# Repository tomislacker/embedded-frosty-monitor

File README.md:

# embedded-frosty-monitor

A portable diagnostic data logger for Frosty Factory 117A/127A/137A frozen-drink
machines. A service tech temporarily installs it inside a machine, lets it run
for days to weeks logging vibration, current draw, temperatures, and
control-state, then pulls the SD card and analyzes the data offline to find
the root cause of an intermittent or hard-to-diagnose fault.

This is not a permanently-installed product. It is a bench/field diagnostic
tool: one unit, moved from machine to machine, that turns "it acts up
sometimes" into a timestamped record of what the compressor, beater motor,
and control chain were actually doing.

## Who this is for

- **Service technicians** who need to capture what a machine does between
  visits, correlate an intermittent symptom (short-cycling, failure to
  freeze, knocking, belt slip) against a timestamp, and bring evidence back
  to the bench instead of a guess.
- **The project owner**, building and maintaining the hardware, firmware, and
  analysis pipeline, and using field data to refine failure-signature
  detection over time.

## What it does

- Logs two AC current channels (beater motor leg, compressor leg) via CT
  clamps, sampled at 1 Hz with transient-burst capture on spikes.
- Logs vibration at the beater drive and the compressor shell via
  accelerometer pods, both as running RMS/peak/band-energy summaries and as
  raw windowed bursts (periodic and trigger-on-event).
- Logs four to five temperatures (cylinder jacket, condenser air in/out,
  ambient, optional hopper) plus compressor discharge line temperature via
  thermocouple.
- Logs drip rate at the drip tube outlet via an optical drop counter — a
  direct, quantitative read on rear cylinder seal wear — plus optional
  under-machine moisture and refrigerant-gas-sensor add-ons.
- Logs digital AC-presence state on the beater leg and the 24VAC contactor
  coil, so control-chain behavior (is the compressor actually trying to run)
  is visible alongside the analog channels.
- Timestamps everything against a battery-backed RTC, independent of network
  time.
- Writes a self-describing record set to a microSD card: a manifest, daily
  CSV channel logs, binary vibration bursts, a vibration summary CSV, and a
  JSONL event log — no proprietary format, no required companion service.
- Lets the tech mark a moment as notable with a physical event button,
  producing a first-class timestamped incident marker independent of any
  later annotation.
- Splits into a reusable "logger core" (the electronics, in an IP65
  enclosure) and cheap, detachable "sensor pods" that take the grease/sugar
  contamination and get replaced, not the core.

## Product tiers

DAQ Pro, described above, is one of four hardware tiers built on the same
firmware, data format, and analysis stack — see
[docs/product-line.md](docs/product-line.md) for the full comparison and
[ADR 0007](docs/adr/0007-product-tier-strategy.md) for the decision behind
the tier structure.

| Tier | BOM (est.) | Install | Status |
|---|---|---|---|
| 1 — Guard | ≈$26 | Permanent, every machine | Designed |
| 2 — Logger | ≈$55–70 | Permanent | Designed |
| 3 — DAQ Pro | $152.60 | Portable (this repo's flagship) | **Built** |
| 4 — Live | $160 WiFi / ≈$210 cellular | Permanent + connectivity | Firmware in progress |

## Repo map

| Path | Owner content | Description |
|---|---|---|
| [`docs/`](docs/) | this doc set | Architecture, ADRs, safety, roadmap, install guides |
| [`docs/architecture/`](docs/architecture/overview.md) | this doc set | System overview and data-flow diagrams |
| [`docs/adr/`](docs/adr/template.md) | this doc set | Architecture decision records |
| [`docs/hardware/`](docs/hardware/) | hardware docs | Wiring, enclosure, sensor placement, BOM |
| [`docs/firmware/`](docs/firmware/architecture.md) | firmware docs | Firmware architecture and on-card data format spec |
| [`docs/install-guides/`](docs/install-guides/137A.md) | install-guide docs | Per-model install procedures (117A/127A/137A) |
| `firmware/` | firmware team | PlatformIO project: FreeRTOS tasks, drivers, storage sinks |
| `hardware/` | hardware team | Schematics, enclosure files, BOM source |
| [`pcb/guard/`](pcb/guard/README.md) | PCB (experimental) | Guard tier custom PCB: SKiDL schematic, scripted layout/DRC, agent-driven design experiment -- unreviewed draft, not fab-ready |
| `analysis/` | analysis team | Offline Python analysis pipeline and tests |

## Quickstart

### Firmware

```
cd firmware
pio run -e esp32-s3-devkitc-1
```

See [`docs/firmware/architecture.md`](docs/firmware/architecture.md) for the
task layout and [`docs/firmware/data-format-spec.md`](docs/firmware/data-format-spec.md)
for the on-card record format.

### Analysis

```
python -m venv .venv && . .venv/bin/activate
pip install -e analysis/
pytest analysis/tests
```

### Installing on a machine

Read [`docs/safety.md`](docs/safety.md) before touching a machine. Then
follow the model-specific procedure in
[`docs/install-guides/137A.md`](docs/install-guides/137A.md).

## Project status

**M0 — docs and repo skeleton.** No hardware has been built or bench-tested
yet; this stage is establishing the architecture, decisions, and safety
constraints the rest of the project builds on.

Milestones:

- **M0** — Docs and skeleton. Architecture, ADRs, safety doc, roadmap; repo
  layout in place. *(current)*
- **M1** — Bench bring-up of real drivers: each sensor/breakout talking to
  the ESP32-S3 on a breadboard, no enclosure, no machine.
- **M2** — Enclosure integration: logger core assembled in its IP65 box,
  sensor pods wired and connectorized, full firmware pipeline exercised on
  the bench.
- **M3** — Bench test on a spare 137A: full install procedure rehearsed on a
  non-production machine.
- **M4** — First field deployment: unit installed in a live machine at a
  customer site for a real diagnostic case.
- **M5** — 117A/127A validation: confirm the sensor placements and
  thresholds generalize across the other two chassis sizes.

See [`docs/roadmap.md`](docs/roadmap.md) for what comes after M5.

## License

Licensed under the Apache License, Version 2.0 — see [`LICENSE`](LICENSE).
Copyright 2026 Ben Tomasik (tomislacker).

You may use, reproduce, modify, and distribute this work, including
commercially, provided you retain the copyright notice, the license text, and
the [`NOTICE`](NOTICE) file in any redistribution, and state any changes you
made. The license covers everything in this repo: firmware, the analysis
package, hardware BOM and pinmap, and the doc set.

The license's "AS IS" disclaimer applies to the hardware designs and install
procedures as much as to the code. This device is installed inside machines
carrying line-voltage AC and refrigerant under pressure — read
[`docs/safety.md`](docs/safety.md) and take responsibility for your own build.

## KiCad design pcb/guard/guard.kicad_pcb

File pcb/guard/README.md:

# FrostSight Guard rev A (draft) -- PCB (experimental)

> **This is an unreviewed draft. It has not been checked by a human EE and
> must not be fabricated as-is.** See
> [docs/compliance.md](../../docs/compliance.md) for the certification
> context this board eventually has to clear, and get a professional EE
> review before sending anything here to a fab. This whole `pcb/guard/`
> tree is an experiment in agent-driven PCB design with a scripted
> verification loop (SKiDL schematic -> pcbnew layout -> `kicad-cli` DRC
> + renders) -- it is deliberately optimized for *reviewability*, not for
> being fab-ready out of the box.

This is the first custom PCB for the Guard tier described in
[docs/product-line.md](../../docs/product-line.md) (Tier 1): a permanent,
every-machine monitor board built around a pre-certified ESP32-C3-MINI-1
module. SELV only -- nothing above 5V ever touches this board.

## Honest status

**What's done:**

- A complete SKiDL schematic ([`schematic.py`](schematic.py)) covering
  every circuit block in the spec: MCU, USB-C power+data with ESD
  protection, 3.3V regulation, CT current-sense front end, 2x DS18B20
  headers, drip-counter header, status/alert LEDs, ack/BOOT/RESET
  buttons, I2C (Qwiic) and UART expansion headers, 2x M3 mounting holes.
- SKiDL ERC passes clean: **0 errors, 0 warnings** (two expected
  advisory warnings are pre-empted with documented, reviewed waivers --
  see the ERC section at the bottom of `schematic.py`).
- A generated KiCad netlist (`guard.net`) and a from-scratch `.kicad_pcb`
  ([`build_board.py`](build_board.py)) with a deliberate, documented
  placement for all 43 components, a ground pour on both copper layers,
  an antenna keep-out rule area, and a scripted attempt at routing the
  short, unambiguous connections.
- `kicad-cli pcb drc` on the routed board: **0 electrical violations**
  (no shorting, no copper clearance violations, no crossing tracks, no
  out-of-range drills/holes). 3 non-electrical DRC nags remain --
  1 courtyard overlap (a mounting hole's 3.45mm-radius assembly-exclusion
  circle just can't clear everything on a board this dense) and 2
  silkscreen-clipped-by-edge nags on the CT jack's own library
  silkscreen, which is expected for a connector whose body intentionally
  overhangs the board edge. Full detail: `drc_report.json`, or run
  `check.sh` yourself.
- Renders inspected and iterated on twice: the first pass had the USB-C
  connector's mating face sitting ~2mm inboard of the board edge instead
  of flush with it; the second pass (current state) fixed that. See
  `renders/top.png` / `renders/bottom.png` / `.svg`.
- A [`bom.csv`](bom.csv) with per-line LCSC estimates and a rollup
  compared against the tier's cost targets.

**What's not done / known limitations:**

- **Routing is partial, on purpose.** The scripted router in
  `build_board.py` only commits a track when it's confident the hop is
  short and won't clip a foreign pad, cross another net's track, or run
  through the antenna keep-out -- otherwise it leaves the connection as
  ratsnest rather than fake a route. Current numbers (regenerate with
  `check.sh` to reconfirm): **20 of 65 point-to-point hops routed**, 3 of
  25 signal/power nets fully routed, 6 partially, 16 left entirely as
  ratsnest (46 unconnected items in the DRC report). GND is handled
  entirely by copper pour instead of discrete traces, which is normal
  practice, not a routing gap. **Finishing routing by hand in the KiCad
  GUI is the single biggest next step before this is fab-ready.**
- **Board is 70x55mm, not the spec's <=60x45mm target.** This is a
  direct, documented consequence of a library gap, not a claim that the
  real board can't hit spec -- see the MCU footprint note below.
- **No thermal analysis.** Nothing has been checked for the AMS1117's
  dropout/dissipation under sustained WiFi TX bursts, copper pour
  thermal relief, or enclosure thermal behavior.
- **No real DFM/panelization review**, no impedance analysis on the USB
  differential pair, no BOM stock/lead-time check beyond LCSC part-number
  estimates.
- **1 cosmetic courtyard overlap and 2 cosmetic silkscreen nags** remain
  in DRC, as noted above -- neither is electrical.

## The MCU footprint substitution -- read this before opening the board

The spec calls for an **ESP32-C3-MINI-1** module. KiCad 10's stock
libraries do not ship a MINI-1 symbol or footprint (they have
ESP32-C3-WROOM-02, ESP32-C3-DevKitM-1, and ESP32-C6-MINI-1, but not
C3-MINI-1). This design uses **RF_Module:ESP32-C3-WROOM-02** as a
stand-in everywhere U1 appears:

- Same ESP32-C3 SoC, same GPIO numbering and strapping behavior
  (GPIO0-10, 18/19 USB, 20/21 UART0) -- every net connection and the GPIO
  table below are electrically representative of the real MINI-1.
- The WROOM-02 footprint is physically **larger** (~18.2x20.2mm) than the
  real MINI-1 (~15.4x20.5mm) and its castellated pad positions do not
  match MINI-1's datasheet pad map. That size difference is the reason
  this board is 70x55mm instead of the spec's 60x45mm target, and the
  antenna keep-out zone in `build_board.py` is sized against the
  WROOM-02's geometry, not MINI-1's.

**Before fabrication, EE review must swap in a real ESP32-C3-MINI-1
footprint** (built from Espressif's datasheet pad map) and re-verify the
antenna keep-out against MINI-1's actual RF section location. Doing that
should let the board shrink back toward the 60x45mm target.

## GPIO assignment (authoritative)

| GPIO | Net | Function | Notes |
|---|---|---|---|
| GPIO0 | `CT_SIG` | ADC1_CH0, CT current sense | through anti-alias RC + bias network |
| GPIO1 | `ONEWIRE` | DS18B20 bus (both JST-XH chains, shared) | single 4.7k pull-up |
| GPIO2 | -- | **reserved, unpopulated** | strapping pin; no load at boot |
| GPIO3 | `DRIP_SIG` | drip-counter pulse in | RC debounced |
| GPIO4 | `LED_STATUS_A` | status LED (green) | ADC1_CH4 unused as analog |
| GPIO5 | `LED_ALERT_A` | alert LED (red) | |
| GPIO6 | `I2C_SCL` | Qwiic expansion | |
| GPIO7 | `I2C_SDA` | Qwiic expansion | |
| GPIO8 | -- | **reserved, unpopulated** | strapping pin; no load at boot |
| GPIO9 | `BTN_BOOT` | BOOT button | conventional strap-to-GND use |
| GPIO10 | `BTN_ACK` | user acknowledge button | |
| GPIO18 | `USB_DM` | native USB D- | fixed function |
| GPIO19 | `USB_DP` | native USB D+ | fixed function |
| GPIO20 | `UART_RX` | debug header | |
| GPIO21 | `UART_TX` | debug header | |
| EN | `EN_RESET` | RESET button (EN-to-GND) | 10k pull-up + 100nF per Espressif ref design |

GPIO2 and GPIO8 -- the two strapping pins other than BOOT/GPIO9 -- are
left completely unpopulated: no resistor, no connector, nothing that
could present a load at boot, per the board spec.

## Design-for-compliance notes

- **SELV only.** Everything on this board runs at 5V or below; mains
  never touches it. USB-C is configured 5V-only via 5.1k CC pulldowns,
  no PD negotiation.
- **Pre-certified module, no custom antenna.** The MCU's onboard PCB
  antenna is used as-is; this design does not attempt a custom antenna,
  which is what keeps the module's existing FCC modular approval valid.
- **ESD protection on every user-touchable connector path**: USBLC6-2
  class protection on USB VBUS/D+/D-; a BAT54S dual-Schottky clamp on the
  CT sense line.
- **No exposed copper test points near the board edge mounting area.**
  Both M3 mounting holes use the `MountingHole_3.2mm_M3` footprint, which
  is a bare drilled hole with no copper pad.

## Repo map

| File | What it is |
|---|---|
| `schematic.py` | SKiDL design-as-code schematic. Run it to regenerate `guard.net`. Heavily commented -- read this first, it's the reviewable schematic. |
| `guard.net` | Generated KiCad netlist (do not hand-edit; regenerate from `schematic.py`). |
| `build_board.py` | pcbnew layout script: placement, ground pours, antenna keep-out, scripted routing. Fully re-runnable -- regenerates `guard.kicad_pcb` from scratch every time. |
| `guard.kicad_pcb` / `.kicad_pro` / `.kicad_prl` | Generated PCB + project files. Open `guard.kicad_pcb` (or the `.kicad_pro`) in KiCad's PCB Editor to inspect/hand-route. |
| `check.sh` | The verification gate: schematic ERC -> board build -> DRC -> renders, in order, with a real non-zero exit on an electrical problem. |
| `drc_report.json` | Latest `kicad-cli pcb drc` output (regenerated by `check.sh`). |
| `bom.csv` | Bill of materials with LCSC estimates and a cost rollup. |
| `renders/` | `top.png` / `bottom.png` (3D-style renders) and `top.svg` / `bottom.svg` (flat copper+silk+edge views), regenerated by `check.sh`. |

## How to run `check.sh`

You need:

1. **KiCad 10** with `kicad-cli` on `PATH`, and its bundled `pcbnew`
   Python module importable from a system `python3` (verify with
   `python3 -c "import pcbnew"`).
2. A separate Python environment with **SKiDL** installed, pointed at
   KiCad's symbol libraries:

   ```
   python3 -m venv pcb/guard/venv   # or wherever you keep it
   source pcb/guard/venv/bin/activate
   pip install skidl
   ```

   SKiDL and `pcbnew` have never needed to coexist in one interpreter
   for this project -- `schematic.py` runs under the SKiDL venv,
   `build_board.py` runs under the system `python3` that has `pcbnew`.
   `schematic.py` itself hard-codes `KICAD_SYMBOL_DIR` (defaulting to
   `/usr/share/kicad/symbols`) so it doesn't depend on shell env vars.

3. Then, from `pcb/guard/`:

   ```
   ./check.sh
   ```

   `check.sh` looks for a SKiDL-capable interpreter at `./venv/bin/python3`
   first, then falls back to whatever's on `PATH`; override with
   `SKIDL_PYTHON=/path/to/python3`. It looks for `pcbnew` on plain
   `python3` by default; override with `PCBNEW_PYTHON=/path/to/python3`
   if yours lives somewhere else.

## How to open this in the KiCad GUI

- **PCB only:** open `guard.kicad_pcb` (or `guard.kicad_pro`) directly in
  KiCad's PCB Editor. Placement, pours, the antenna keep-out zone, and
  whatever the scripted router routed are all there to inspect, and it's
  a normal KiCad board file -- hand-routing the rest, nudging placement,
  and rerunning DRC all work exactly like any other KiCad project.
- **No `.kicad_sch` exists.** The schematic is `schematic.py` itself (the
  SKiDL source) plus the generated `guard.net` netlist -- there's no
  KiCad schematic file to open in the Schematic Editor. If a real KiCad
  schematic sheet becomes useful later (e.g. so a human can redline it
  directly), generating one from `guard.net` is a reasonable next step,
  not something this experiment did.

## Next steps

1. **Professional EE review** (this board's one paid hour) -- start with
   this README's limitations list and the MCU footprint-substitution
   note above.
2. **Swap in a real ESP32-C3-MINI-1 footprint** built from Espressif's
   datasheet pad map, re-verify the antenna keep-out against it, and see
   how close the board comes back to the 60x45mm target.
3. **Finish routing.** 20 of 65 hops are routed; the rest need either a
   smarter scripted router or hand-routing in the KiCad GUI.
4. **JLCPCB DFM upload** once routing is complete and the footprint swap
   above is done -- their DFM checker will catch fab-specific issues
   (soldermask, silkscreen-on-pad, panelization) that a generic DRC run
   doesn't.

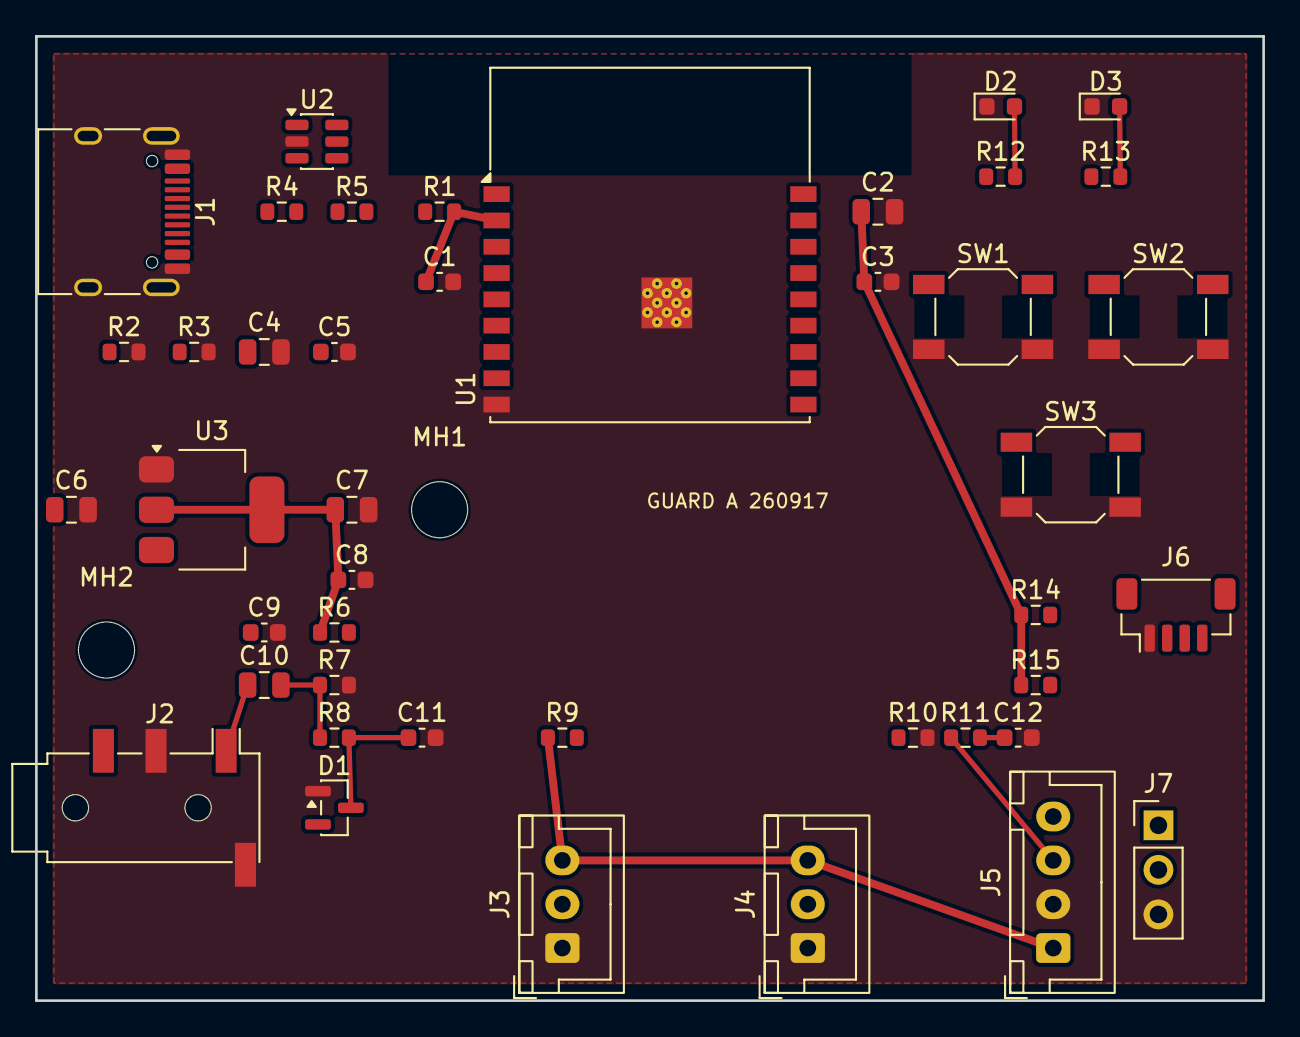
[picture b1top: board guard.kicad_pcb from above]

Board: 2 copper layers, 70.0 x 55.0 mm, 45 parts (0 on the bottom side), 26 nets.

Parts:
C1, C3, C5, C8, C11, C12: 100nF; C_0603_1608Metric
C2, C4, C6, C10: 10uF; C_0805_2012Metric
C7: 22uF; C_0805_2012Metric
C9: 1uF; C_0603_1608Metric
D1: BAT54S; SOT-23
D2: Status LED (green); LED_0603_1608Metric
D3: Alert LED (red); LED_0603_1608Metric
J1: USB-C receptacle (5V power + USB2.0 data, no PD); USB_C_Receptacle_HRO_TYPE-C-31-M-12
J2: 3.5mm TRS (SCT-013-020 burden output, 1V RMS @ ra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; Jack_3.5mm_PJ320D_Horizontal
J3: DS18B20 chain 1 (pin1 GND / pin2 DQ / pin3 3V3); JST_XH_B3B-XH-A_1x03_P2.50mm_Vertical
J4: DS18B20 chain 2 (pin1 GND / pin2 DQ / pin3 3V3); JST_XH_B3B-XH-A_1x03_P2.50mm_Vertical
J5: Drip counter (pin1 3V3 / pin2 GND / pin3 SIG / pi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; JST_XH_B4B-XH-A_1x04_P2.50mm_Vertical
J6: I2C expansion, Qwiic pinout (pin1 GND / pin2 3V3 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; JST_SH_BM04B-SRSS-TB_1x04-1MP_P1.00mm_Vertical
J7: UART debug (pin1 TX / pin2 RX / pin3 GND); PinHeader_1x03_P2.54mm_Vertical
MH1, MH2: MountingHole_3.2mm_M3
R1, R6, R7, R10: 10k; R_0603_1608Metric
R2, R3: 5.1k; R_0603_1608Metric
R4, R5: 22; R_0603_1608Metric
R8, R11: 1k; R_0603_1608Metric
R9, R14, R15: 4.7k; R_0603_1608Metric
R12, R13: 330; R_0603_1608Metric
SW1: Ack button (user); SW_SPST_SKQG_WithoutStem
SW2: BOOT button (GPIO9, conventional strap-to-GND); SW_SPST_SKQG_WithoutStem
SW3: RESET button (EN-to-GND); SW_SPST_SKQG_WithoutStem
U1: ESP32-C3-MINI-1 (schematic symbol: ESP32-C3-WROOM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; ESP32-C3-WROOM-02
U2: USBLC6-2SC6; SOT-23-6
U3: AMS1117-3.3; SOT-223

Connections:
+3V3: C2.1, C3.1, C7.1, C8.1, D1.2, J3.3, J4.3, J5.1, J6.2, R1.1, R6.1, R9.1, R14.1, R15.1, U1.1, U3.2, U3.4
BTN_ACK: SW1.1, U1.10
BTN_BOOT: SW2.1, U1.8
CC1: J1.A5, R2.1
CC2: J1.B5, R3.1
CT_BIAS: C9.1, C10.2, R6.2, R7.1, R8.1
CT_RAW: C10.1, J2.T
CT_SIG: C11.1, D1.3, R8.2, U1.18
DRIP_RAW: J5.3, R10.1, R11.1
DRIP_SIG: C12.1, R11.2, U1.15
EN_RESET: C1.1, R1.2, SW3.1, U1.2
GND: C1.2, C2.2, C3.2, C4.2, C5.2, C6.2, C7.2, C8.2, C9.2, C11.2, C12.2, D1.1, D2.1, D3.1, J1.A1, J1.A12, J1.B1, J1.B12, J1.SH, J2.R1, J2.S, J3.1, J4.1, J5.2, J6.1, J7.3, R2.2, R3.2, R7.2, R10.2, SW1.2, SW2.2, SW3.2, U1.9, U1.19, U2.2, U3.1
I2C_SCL: J6.4, R14.2, U1.5
I2C_SDA: J6.3, R15.2, U1.6
LED_ALERT_A: R13.1, U1.4
LED_STATUS_A: R12.1, U1.3
unnamed: D2.2, R12.2
unnamed: D3.2, R13.2
ONEWIRE: J3.2, J4.2, R9.2, U1.17
UART_RX: J7.2, U1.11
UART_TX: J7.1, U1.12
USB_DM: R5.2, U1.13
USB_DM_CONN: J1.A7, J1.B7, R5.1, U2.3, U2.4
USB_DP: R4.2, U1.14
USB_DP_CONN: J1.A6, J1.B6, R4.1, U2.1, U2.6
VBUS: C4.1, C5.1, C6.1, J1.A4, J1.A9, J1.B4, J1.B9, U2.5, U3.3

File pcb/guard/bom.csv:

Designators,Qty,Value,Footprint,LCSC Part # (estimate unless noted),Unit Price USD (est.),Ext. Price USD (est.),Notes
U1,1,ESP32-C3-MINI-1,RF_Module:ESP32-C3-MINI-1 (schematic uses ESP32-C3-WROOM-02 stand-in -- see README),C2934569,1.85,1.85,"Pre-certified module, onboard PCB antenna. Real MINI-1 footprint not in stock KiCad libs -- see README limitations."
J1,1,USB-C receptacle 16P,Connector_USB:USB_C_Receptacle_HRO_TYPE-C-31-M-12,C165948,0.12,0.12,5V/USB2.0 only; no PD IC
U2,1,USBLC6-2SC6,Package_TO_SOT_SMD:SOT-23-6,C2827654,0.06,0.06,USB ESD protection (VBUS/D+/D-)
U3,1,AMS1117-3.3,Package_TO_SOT_SMD:SOT-223,C6186,0.06,0.06,>=1A rated 3.3V LDO
D1,1,BAT54S,Package_TO_SOT_SMD:SOT-23,C8598,0.02,0.02,Dual Schottky clamp on CT_SIG
D2,1,LED green 0603,LED_SMD:LED_0603_1608Metric,C72043,0.01,0.01,Status LED
D3,1,LED red 0603,LED_SMD:LED_0603_1608Metric,C2286,0.01,0.01,Alert LED
"SW1,SW2,SW3",3,Tactile switch SMD 6x6mm,Button_Switch_SMD:SW_SPST_SKQG_WithoutStem,C318884,0.03,0.09,Ack / BOOT / RESET buttons
J2,1,3.5mm TRS jack (THT),Connector_Audio:Jack_3.5mm_PJ320D_Horizontal,C144396,0.10,0.10,SCT-013-020 CT input; likely hand-solder/THT reflow, not a basic SMT part
"J3,J4",2,JST-XH 3-pin vertical (THT),Connector_JST:JST_XH_B3B-XH-A_1x03_P2.50mm_Vertical,C158126,0.05,0.10,DS18B20 chain headers
J5,1,JST-XH 4-pin vertical (THT),Connector_JST:JST_XH_B4B-XH-A_1x04_P2.50mm_Vertical,C158128,0.06,0.06,Drip counter header
J6,1,JST-SH 4-pin vertical (THT),Connector_JST:JST_SH_BM04B-SRSS-TB_1x04-1MP_P1.00mm_Vertical,C160404,0.06,0.06,I2C/Qwiic expansion header
J7,1,Pin header 1x3 2.54mm (THT),Connector_PinHeader_2.54mm:PinHeader_1x03_P2.54mm_Vertical,C124378,0.02,0.02,UART debug header
"R4,R5",2,22R 0603,Resistor_SMD:R_0603_1608Metric,C25744,0.002,0.004,USB D+/D- series termination
"R12,R13",2,330R 0603,Resistor_SMD:R_0603_1608Metric,C22775,0.002,0.004,LED series resistors
"R8,R11",2,1k 0603,Resistor_SMD:R_0603_1608Metric,C21190,0.002,0.004,CT anti-alias / drip series
"R9,R14,R15",3,4.7k 0603,Resistor_SMD:R_0603_1608Metric,C23162,0.002,0.006,1-Wire pull-up / I2C pull-ups
"R2,R3",2,5.1k 0603,Resistor_SMD:R_0603_1608Metric,C25900,0.002,0.004,USB-C CC1/CC2 pulldowns
"R1,R6,R7,R10",4,10k 0603,Resistor_SMD:R_0603_1608Metric,C25741,0.002,0.008,EN pull-up / CT bias divider / drip pulldown
"C1,C3,C8,C11,C12",5,100nF 0603,Capacitor_SMD:C_0603_1608Metric,C14663,0.003,0.015,Decoupling / anti-alias / debounce
C9,1,1uF 0603,Capacitor_SMD:C_0603_1608Metric,C15849,0.01,0.01,CT bias node decoupling
"C2,C4,C6,C10",4,10uF 0805,Capacitor_SMD:C_0805_2012Metric,C19702,0.02,0.08,Bulk decoupling / AC-coupling
C7,1,22uF 0805,Capacitor_SMD:C_0805_2012Metric,C45783,0.03,0.03,AMS1117 output cap
"MH1,MH2",2,M3 mounting hole (NPTH),MountingHole:MountingHole_3.2mm_M3,N/A -- drilled feature not a stocked part,0.00,0.00,No copper at hole per compliance note
,,,,,,,
,,,,,COMPONENTS SUBTOTAL,2.73,
,,,,,Bare PCB fab (2-layer 70x55mm; small-batch estimate),2.00,
,,,,,JLCPCB SMT assembly service fee (amortized; small-batch estimate),9.00,
,,,,,ESTIMATED PCBA TOTAL (small batch),13.73,
,,,,,,,
,,,,,vs. docs/product-line.md Guard module-based BOM (~$26; includes enclosure/PSU/wiring not this PCB),,
,,,,,vs. docs/product-line.md $10-15 PCBA target,within target band at small-batch assembly pricing assumed above,,

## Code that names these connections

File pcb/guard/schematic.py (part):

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
GPIO ASSIGNMENT (authoritative -- mirrored in README.md)

  GPIO0   ADC1_CH0  CT_SIG        analog, through anti-alias RC + bias net
  GPIO1             ONEWIRE       DS18B20 bus (both JST-XH chains, shared)
  GPIO2             RESERVED      strapping pin -- left unconnected (NC)
  GPIO3             DRIP_SIG      drip-counter pulse in, RC debounced
  GPIO4   ADC1_CH4  LED_STATUS    green status LED (ADC channel unused)
  GPIO5             LED_ALERT     red alert LED
  GPIO6             I2C_SCL       Qwiic expansion header
  GPIO7             I2C_SDA       Qwiic expansion header
  GPIO8             RESERVED      strapping pin -- left unconnected (NC)
  GPIO9             BTN_BOOT      BOOT button, conventional strap-to-GND use
  GPIO10            BTN_ACK       user acknowledge button
  GPIO18            USB_DM        native USB, fixed function
  GPIO19            USB_DP        native USB, fixed function
  GPIO20            UART_RX       debug header
  GPIO21            UART_TX       debug header
  EN                RESET         reset button (EN-to-GND) + 10k pull-up +
                                   100nF per Espressif reference design

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VBUS.drive = pin_drives.POWER
V3V3.drive = pin_drives.POWER

CT_SIG = Net("CT_SIG")  # to MCU ADC1_CH0 (GPIO0), post anti-alias filter
ONEWIRE = Net("ONEWIRE")  # shared DS18B20 bus, GPIO1
DRIP_SIG = Net("DRIP_SIG")  # debounced drip pulse, GPIO3
LED_STATUS = Net("LED_STATUS_A")  # anode side of status LED, GPIO4
LED_ALERT = Net("LED_ALERT_A")  # anode side of alert LED, GPIO5
I2C_SCL = Net("I2C_SCL")  # GPIO6
I2C_SDA = Net("I2C_SDA")  # GPIO7
BTN_BOOT = Net("BTN_BOOT")  # GPIO9
BTN_ACK = Net("BTN_ACK")  # GPIO10
USB_DM = Net("USB_DM")  # GPIO18, ESD-protected
USB_DP = Net("USB_DP")  # GPIO19, ESD-protected
UART_RX = Net("UART_RX")  # GPIO20
UART_TX = Net("UART_TX")  # GPIO21
EN_RESET = Net("EN_RESET")  # MCU EN pin


# ---------------------------------------------------------------------
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
# =======================================================================
# BLOCK 4 -- CT input x1: 3.5mm TRS jack, bias network, anti-alias RC,
# clamp protection, into MCU ADC1 (GPIO0/CT_SIG).
# =======================================================================
ct_jack = Part(
    "Connector_Audio", "AudioJack3",
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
